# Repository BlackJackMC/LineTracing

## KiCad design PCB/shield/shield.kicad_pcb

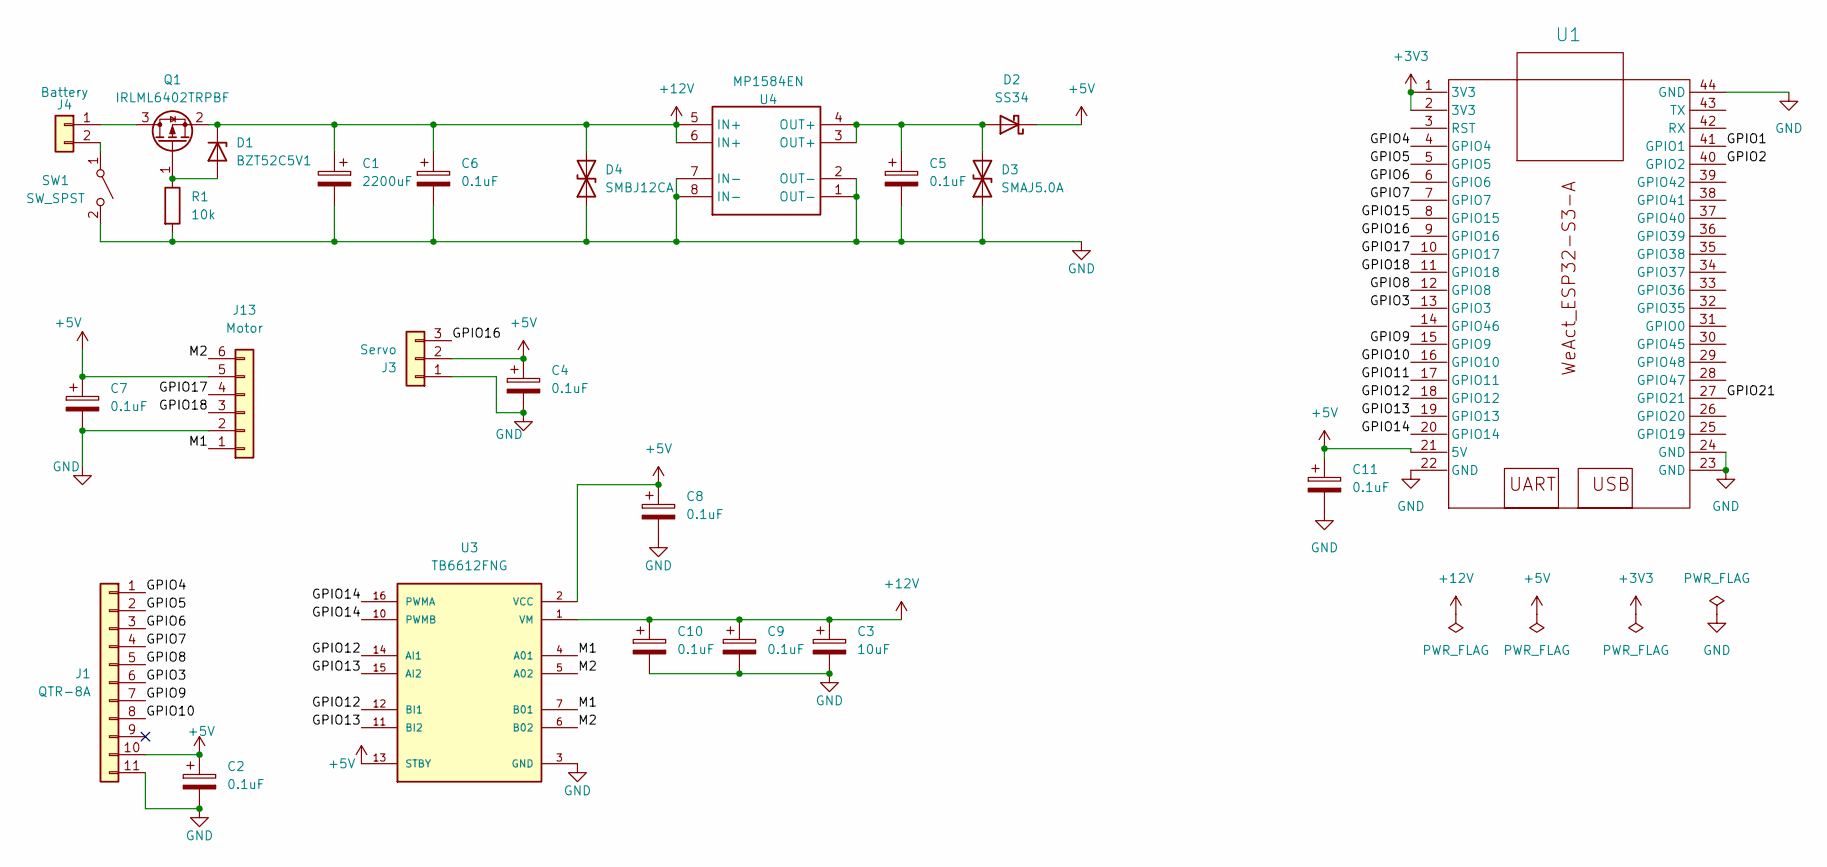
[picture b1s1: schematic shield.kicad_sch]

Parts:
C1: 2200uF; CP_Radial_D10.0mm_P5.00mm
C2, C4, C5, C6, C7, C8, C9, C10, C11: 0.1uF; C_0805_2012Metric_Pad1.18x1.45mm_HandSolder
C3: 10uF; CP_Elec_4x5.4
D1: BZT52C5V1; D_SOD-123
D2: SS34; D_SMA
D3: SMAJ5.0A; D_SMB_Handsoldering
D4: SMBJ12CA; D_SMB_Handsoldering
J1: QTR-8A; JST_XH_B11B-XH-A_1x11_P2.50mm_Vertical
J3: Servo; JST_XH_B3B-XH-A_1x03_P2.50mm_Vertical
J4: Battery; TerminalBlock_Phoenix_MKDS-1,5-2_1x02_P5.00mm_Horizontal
J13: Motor; JST_XH_B6B-XH-A_1x06_P2.50mm_Vertical
Q1: IRLML6402TRPBF; SOT-23-3
R1: 10k; R_0603_1608Metric_Pad0.98x0.95mm_HandSolder
SW1: SW_SPST; SW_RF1-1A-DC-2-R-1
U1: WeAct-ESP32-S3-A
U3: TB6612FNG; MODULE_ROB-14450; PARTREV 11-13-17
U4: MP1584EN

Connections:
+3V3: U1.1 (3V3), U1.2 (3V3)
+5V: C2.1, C4.1, C7.1, C8.1, C11.1, D2.1 (K), J1.10, J3.2, J13.5, U1.21 (5V), U3.2 (VCC), U3.13 (STBY)
+12V: C1.1, C3.1, C6.1, C9.1, C10.1, D1.1 (K), D4.2 (A2), Q1.2 (S), U3.1 (VM), U4.5 (IN+), U4.6 (IN+)
/GPIO1: U1.41 (GPIO1)
/GPIO2: U1.40 (GPIO2)
/GPIO3: J1.6, U1.13 (GPIO3)
/GPIO4: J1.1, U1.4 (GPIO4)
/GPIO5: J1.2, U1.5 (GPIO5)
/GPIO6: J1.3, U1.6 (GPIO6)
/GPIO7: J1.4, U1.7 (GPIO7)
/GPIO8: J1.5, U1.12 (GPIO8)
/GPIO9: J1.7, U1.15 (GPIO9)
/GPIO10: J1.8, U1.16 (GPIO10)
/GPIO11: U1.17 (GPIO11)
/GPIO12: U1.18 (GPIO12), U3.12 (BI1), U3.14 (AI1)
/GPIO13: U1.19 (GPIO13), U3.11 (BI2), U3.15 (AI2)
/GPIO14: U1.20 (GPIO14), U3.10 (PWMB), U3.16 (PWMA)
/GPIO15: U1.8 (GPIO15)
/GPIO16: J3.3, U1.9 (GPIO16)
/GPIO17: J13.4, U1.10 (GPIO17)
/GPIO18: J13.3, U1.11 (GPIO18)
/GPIO21: U1.27 (GPIO21)
/M1: J13.1, U3.4 (A01), U3.7 (B01)
/M2: J13.6, U3.5 (A02), U3.6 (B02)
GND: C1.2, C2.2, C3.2, C4.2, C5.2, C6.2, C7.2, C8.2, C9.2, C10.2, C11.2, D3.1 (A1), D4.1 (A1), J1.11, J3.1, J13.2, R1.2, SW1.2 (B), U1.22 (GND), U1.23 (GND), U1.24 (GND), U1.44 (GND), U3.3 (GND), U3.8 (GND), U3.9 (GND), U4.1 (OUT-), U4.2 (OUT-), U4.7 (IN-), U4.8 (IN-)
unnamed: D1.2 (A), Q1.1 (G), R1.1
unnamed: C5.1, D2.2 (A), D3.2 (A2), U4.3 (OUT+), U4.4 (OUT+)
unnamed: J4.1, Q1.3 (D)
unnamed: J4.2, SW1.1 (A)

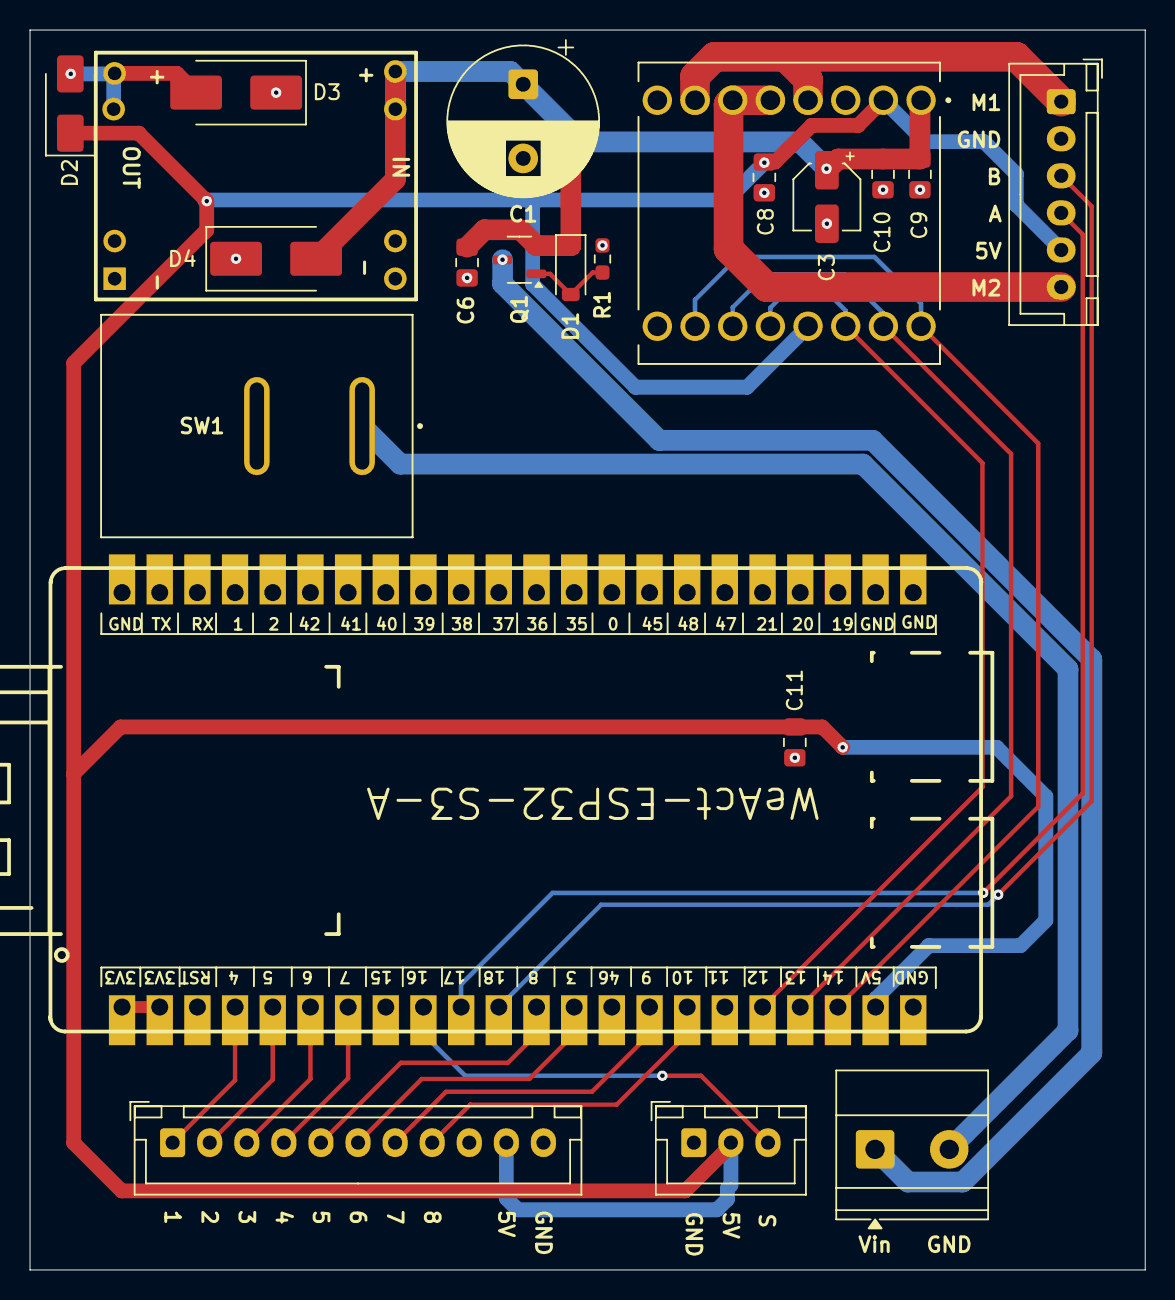
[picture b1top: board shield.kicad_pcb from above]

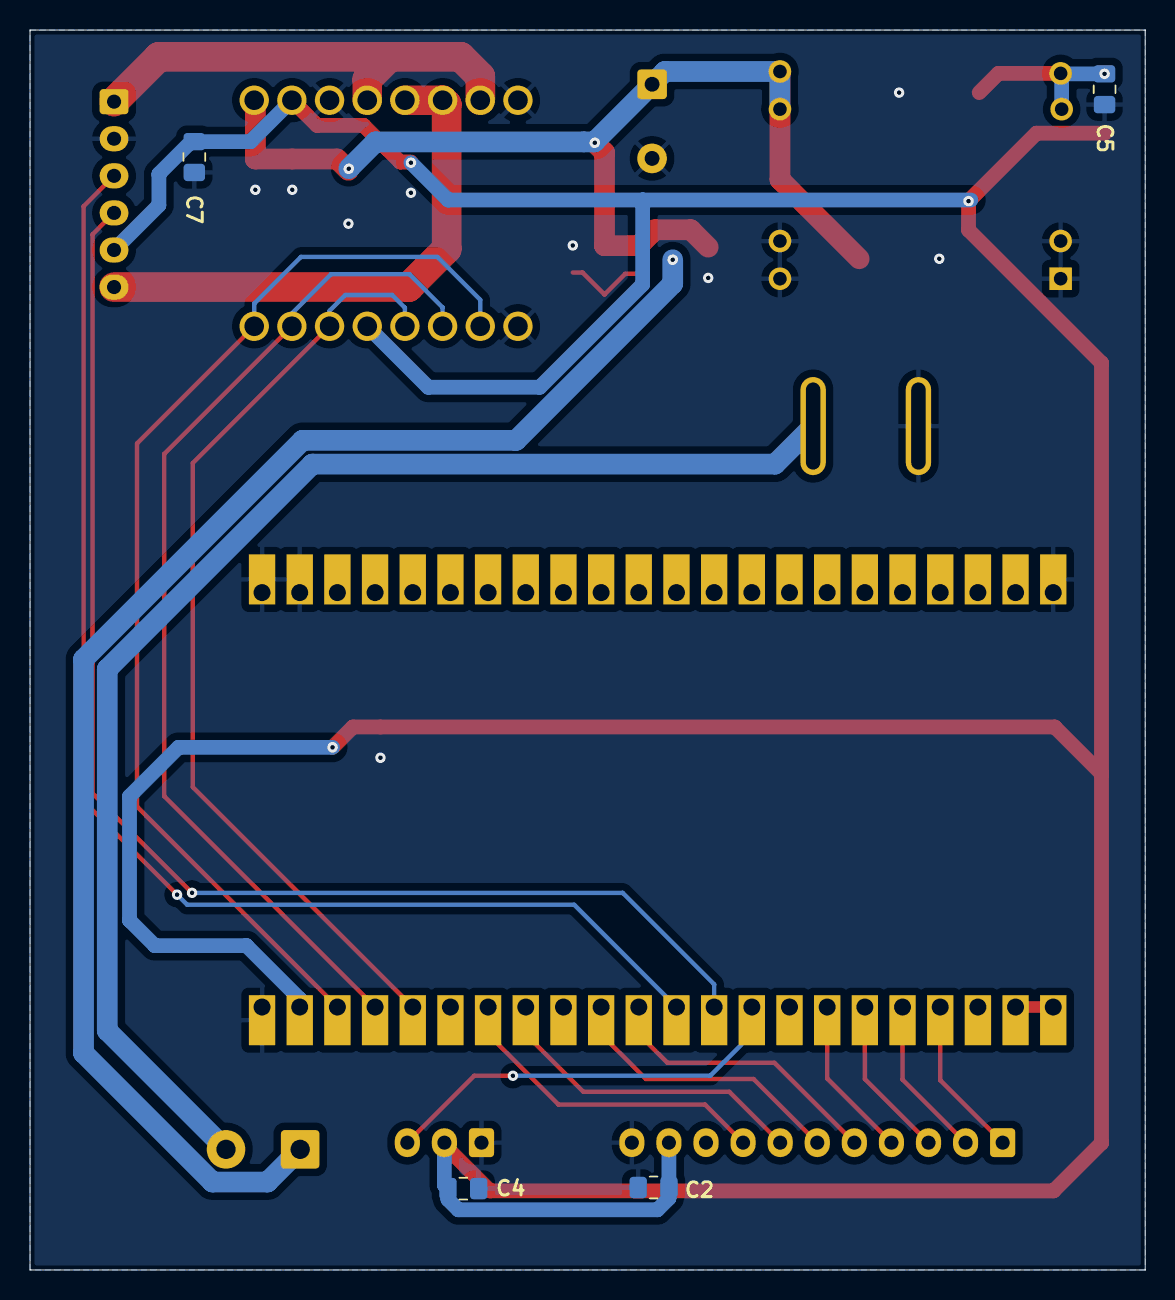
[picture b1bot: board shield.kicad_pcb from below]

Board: 2 copper layers, 75.2 x 83.6 mm, 25 parts (4 on the bottom side), 24 nets.

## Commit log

2025-07-23 feat: add pcb schematic
2025-07-24 feat: traffic light system design file on drawio
2025-07-24 feat: Added design.drawio
2025-07-24 feat: remove trafficlight.drawio
2025-07-24 feat: add pcb footprint
2025-07-24 fix: fix length between 2 esp rails
2025-07-24 wip: pcb tracks
2025-07-24 wip: adding tracks on pcb, adding 7805 regulator
2025-07-25 feat: added pcb traces and remove lm2596s
    Added all required pcb traces.
    Remove LM2596S footprint
    Added LM7805 5V regulator
2025-07-25 feat: added silkscreen labels
2025-07-27 feat: added a button
    Updated button switch THT library
    Added a button connected to GPIO15
2025-07-27 fix: increased distance between esp rails
2025-07-28 feat: changed 5.5 jack to domino terminal
2025-07-28 wip: adding reverse polar protection
    Added 1N5822 to protect reverse polar
2025-08-02 feat: change THT to SMD
    Changed LM7805 to AMS1117
    Changed THT capacitor to SMD capacitor
2025-08-02 feat: add basic traffic light logic (not tested)
2025-08-02 chore: complete implement traffic control, not able to test
2025-08-04 feat: added socket for joystick module
2025-08-05 feat: add lcd oled screen socket
2025-08-06 feat: change vcc trace width
2025-08-06 feat: change AMS1117 to LM2596S
2025-08-06 wip: fixing multiple gpio traces
2025-08-06 feat: change pcb trace width; change sensors input voltage
2025-08-06 feat: idk what I change but it is probably a minor one
2025-08-07 feat: update lib
2025-08-08 chore: tested
2025-08-08 other: leftover
2025-08-08 feat: distance sensor complete, not tested
2025-08-08 chore: fix distance sensor
2025-08-08 feat: change header file name to pascal case
2025-08-11 feat: espnow, not tested
2025-08-18 feat: make pcb smaller
2025-12-18 feat: change pcb design
2025-12-30 wip: commit to change workplace
2026-01-03 wip: commit to change workspace
2026-01-05 feat: change pcb design, use tb6612fng for controlling motor and mosfet for reverse polar protection
2026-01-06 feat: change pcb design, make pcb smaller by removing joystick and screen
2026-01-11 feat: refactoring code
2026-01-12 feat: refactor code complete, not tested due to light not on
2026-01-14 feat: tested with 1 light
2026-01-17 minor: change pcb library directory
2026-01-18 fix: add pcb library to git
2026-01-20 feat: change LM2596S to MP1584EN; change to 2-layer pcb
2026-01-22 feat: change esp32 footprint using altium-based lib
2026-01-23 feat: rearrange pcb footprints; change mosfet
2026-01-24 minor: add measurement in pcb drawing
2026-02-25 changed to esp now
2026-03-05 fix: fix tb6612fng power input
2026-04-06 feat: change components and pcb design
    - Change step-down circuit to LM2596
    - Change motor controller from TB6612FNG to L298N
    - Add L298N interface
    - Change all components to THT
2026-04-13 feat: fix some bugs and add some features in pcb design
2026-04-18 feat: ws client and wifi
2026-04-19 WIP(car): testing components
